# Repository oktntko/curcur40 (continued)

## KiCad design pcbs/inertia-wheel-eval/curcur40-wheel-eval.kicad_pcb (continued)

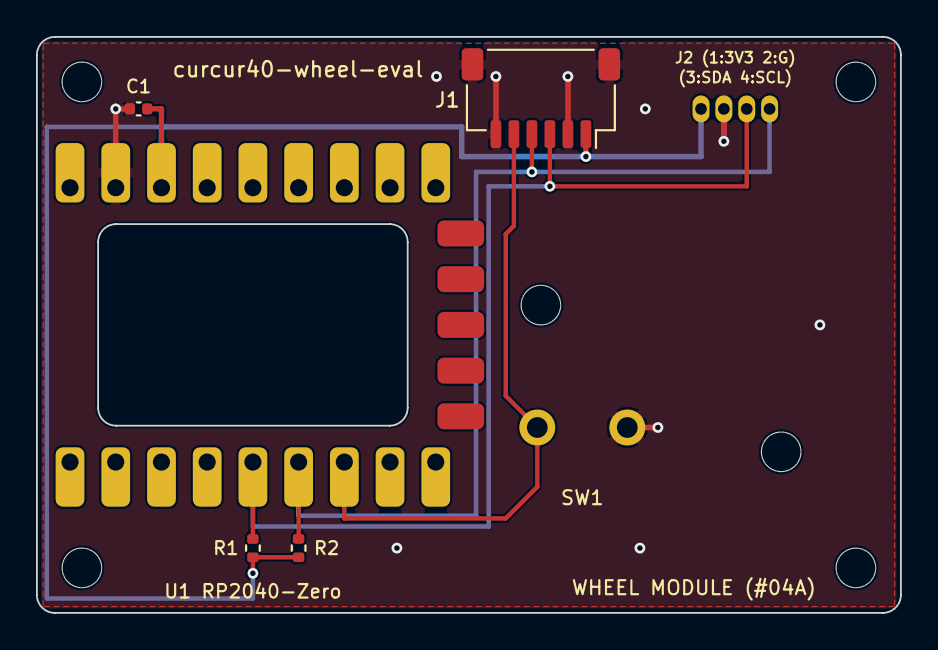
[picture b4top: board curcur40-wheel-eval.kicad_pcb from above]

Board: 2 copper layers, 48.0 x 32.0 mm, 13 parts (0 on the bottom side), 5 nets.

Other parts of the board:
H1, H2, H3, H4, H5, H6: MountingHole; MountingHole_2.2mm_M2

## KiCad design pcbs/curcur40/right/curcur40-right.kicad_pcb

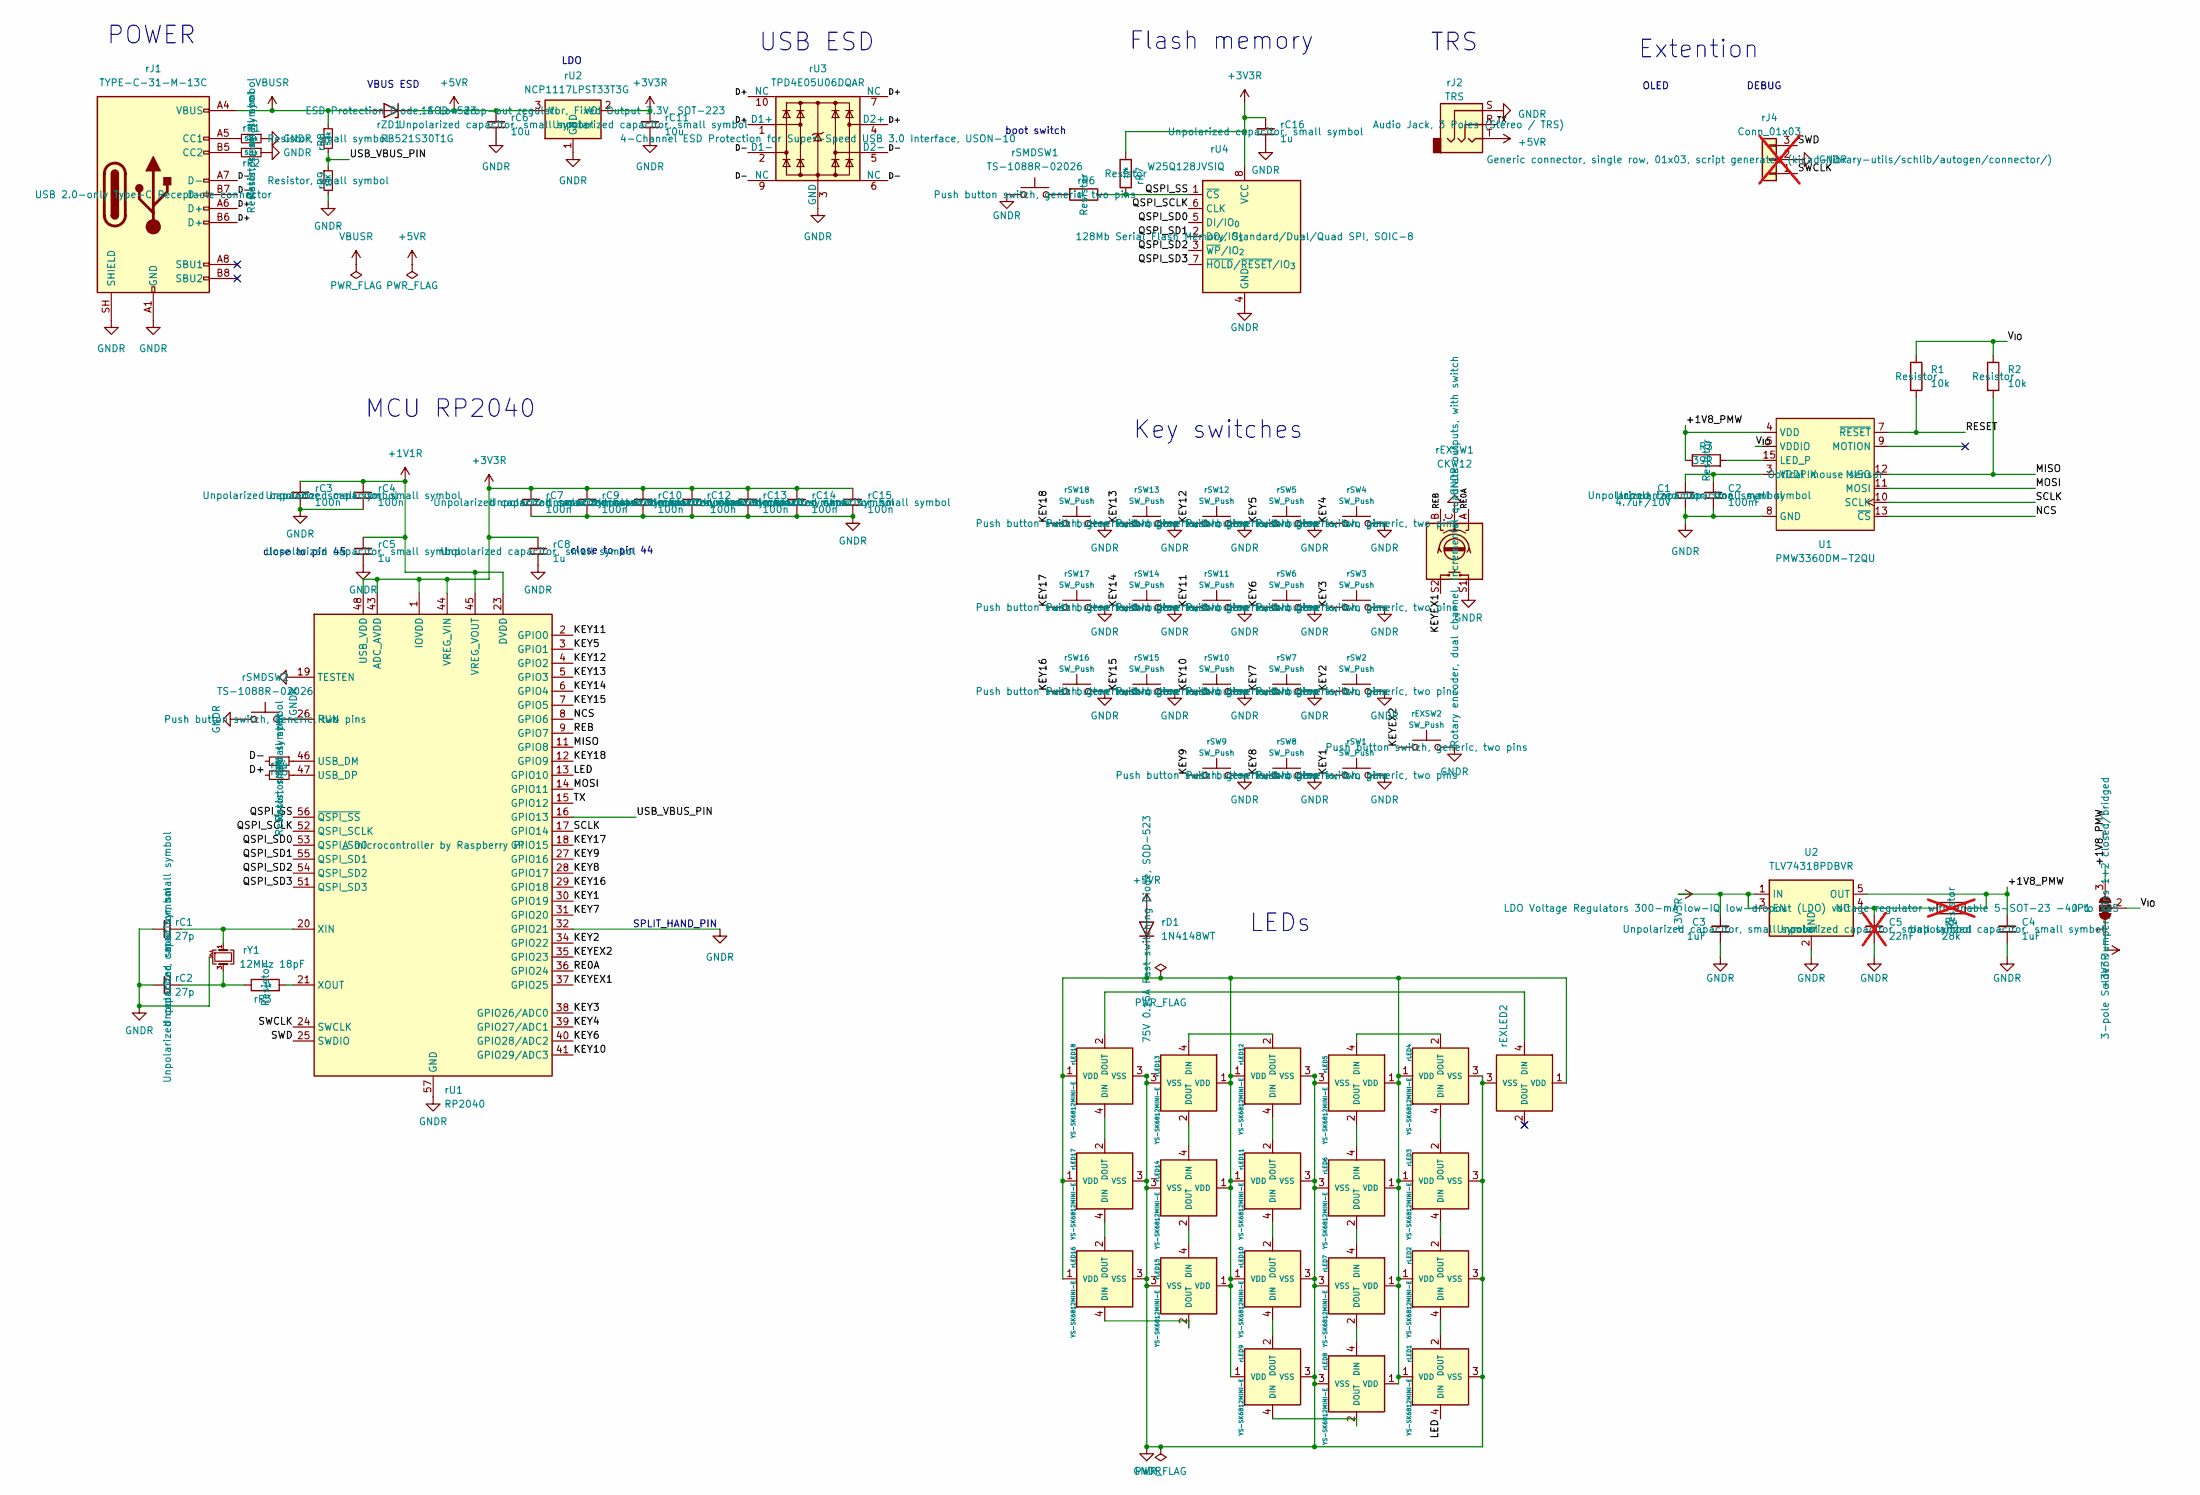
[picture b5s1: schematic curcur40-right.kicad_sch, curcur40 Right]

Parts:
C1: 4.7uF/10V; C_0603_1608Metric_Pad1.08x0.95mm_HandSolder; Mfr. # CL10A475KO8NNNC; LCSC C19666
C2: 100nF; C_0603_1608Metric_Pad1.08x0.95mm_HandSolder; Mfr. # CC0603KRX7R9BB104; LCSC C14663
C3, C4: 1uF; C_0603_1608Metric_Pad1.08x0.95mm_HandSolder; Mfr. # CL10A105KB8NNNC; LCSC C15849
C5: 22nF; C_0603_1608Metric_Pad1.08x0.95mm_HandSolder; Mfr. # CL10B223KB8NNNC; LCSC C21122; not fitted
JP1: SolderJumper_3_Bridged12; SolderJumper-3_P1.3mm_Bridged12_RoundedPad1.0x1.5mm_NumberL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
R1, R2: 10k; R_0603_1608Metric_Pad0.98x0.95mm_HandSolder; Mfr. # 0603WAF1002T5E; LCSC C25804
R3: 39R; R_0603_1608Metric_Pad0.98x0.95mm_HandSolder; Mfr. # 0603WAF390JT5E; LCSC C23154
R4: 28k; R_0603_1608Metric_Pad0.98x0.95mm_HandSolder; not fitted
U1: PMW3360DM-T2QU; PMW3360DM-T2QU_16Pin
U2: TLV74318PDBVR; SOT-23-5; Mfr. # TLV74318PDBVR; LCSC C485152
rC1, rC2: 27p; C_0402_1005Metric
rC3, rC4, rC7, rC9, rC10, rC12, rC13, rC14, rC15: 100n; C_0402_1005Metric
rC5, rC8, rC16: 1u; C_0402_1005Metric
rC6, rC11: 10u; C_0402_1005Metric
rD1: 1N4148WT; D_SOD-523; JLCPCB Part # C232841
rEXLED2: YS-SK6812MINI-E
rEXSW1: CKW12; RotaryEncoder_Switch_CKW12
rEXSW2: SW_Push; keyswitch_choc12_hotswap_1u
rJ1: TYPE-C-31-M-13C; USB_C_Receptacle_TYPE-C-31-M-13C; JLCPCB Part # C2848620
rJ2: TRS; Jack_PJ-398A-5A_PJ-399B-6A; JLCPCB Part # C128994
rJ4: Conn_01x03; PinHeader_1x03_P2.54mm_Vertical; not fitted
rLED1, rLED2, rLED3, rLED4, rLED5, rLED6, rLED7, rLED8, rLED9, rLED10, rLED11, rLED12, rLED13, rLED14, rLED15, rLED16, rLED17, rLED18: YS-SK6812MINI-E
rR1, rR2: 5.1k; R_0402_1005Metric
rR3, rR6: 1k; R_0402_1005Metric
rR4, rR5: 27; R_0402_1005Metric
rR7: 10k; R_0402_1005Metric
rR8: 5.6k; R_0402_1005Metric
rR9: 10K; R_0402_1005Metric
rSMDSW1, rSMDSW2: TS-1088R-02026; JLCPCB Part # C455280
rSW1, rSW2, rSW3, rSW4, rSW5, rSW6, rSW7, rSW8, rSW9, rSW10, rSW11, rSW12, rSW13, rSW14, rSW15, rSW16, rSW17, rSW18: SW_Push; keyswitch_choc12_hotswap_1u
rU1: RP2040; QFN-56-1EP_7x7mm_P0.4mm_EP3.2x3.2mm; JLCPCB Part # C2040
rU2: NCP1117LPST33T3G; SOT-223-3_TabPin2; JLCPCB Part # C146799
rU3: TPD4E05U06DQAR; USON-10_2.5x1.0mm_P0.5mm; JLCPCB Part # C138714
rU4: W25Q128JVSIQ; SOIC-8_5.3x5.3mm_P1.27mm; JLCPCB Part # C113767
rY1: 12MHz 18pF; Crystal_SMD_3225-4Pin_3.2x2.5mm; MFR.Part # Q22FA23V0041800; JLCPCB Part # C91749
rZD1: RB521S30T1G; D_SOD-523; JLCPCB Part # C145179

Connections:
+1V1R: rC3.1, rC4.1, rC5.1, rU1.23 (DVDD), rU1.45 (VREG_VOUT), rU1.50 (DVDD)
+3V3R: C3.1, JP1.1 (A), U2.1 (IN), U2.3 (EN), rC7.1, rC8.1, rC9.1, rC10.1, rC11.1, rC12.1, rC13.1, rC14.1, rC15.1, rC16.1, rR7.2, rU1.1 (IOVDD), rU1.10 (IOVDD), rU1.22 (IOVDD), rU1.33 (IOVDD), rU1.42 (IOVDD), rU1.43 (ADC_AVDD), rU1.44 (VREG_VIN), rU1.48 (USB_VDD), rU1.49 (IOVDD), rU2.2 (VO), rU4.8 (VCC)
+5VR: rC6.1, rD1.2 (A), rJ2.T, rU2.3 (VI), rZD1.1 (K)
/+1V8_PMW: C4.1, JP1.3 (B), R3.1, R4.1, U1.4 (VDD), U2.5 (OUT)
/D+: rJ1.A6 (D+), rJ1.B6 (D+), rR4.1, rU3.1 (D1+), rU3.4 (D2+), rU3.7 (NC), rU3.10 (NC)
/D-: rJ1.A7 (D-), rJ1.B7 (D-), rR5.2, rU3.2 (D1-), rU3.5 (D2-), rU3.6 (NC), rU3.9 (NC)
/KEY1: rSW1.1, rU1.30 (GPIO19)
/KEY2: rSW2.1, rU1.34 (GPIO22)
/KEY3: rSW3.1, rU1.38 (GPIO26/ADC0)
/KEY4: rSW4.1, rU1.39 (GPIO27/ADC1)
/KEY5: rSW5.1, rU1.3 (GPIO1)
/KEY6: rSW6.1, rU1.40 (GPIO28/ADC2)
/KEY7: rSW7.1, rU1.31 (GPIO20)
/KEY8: rSW8.1, rU1.28 (GPIO17)
/KEY9: rSW9.1, rU1.27 (GPIO16)
/KEY10: rSW10.1, rU1.41 (GPIO29/ADC3)
/KEY11: rSW11.1, rU1.2 (GPIO0)
/KEY12: rSW12.1, rU1.4 (GPIO2)
/KEY13: rSW13.1, rU1.5 (GPIO3)
/KEY14: rSW14.1, rU1.6 (GPIO4)
/KEY15: rSW15.1, rU1.7 (GPIO5)
/KEY16: rSW16.1, rU1.29 (GPIO18)
/KEY17: rSW17.1, rU1.18 (GPIO15)
/KEY18: rSW18.1, rU1.12 (GPIO9)
/KEYEX1: rEXSW1.S2, rU1.37 (GPIO25)
/KEYEX2: rEXSW2.1, rU1.35 (GPIO23)
/LED: rLED1.4 (DIN), rU1.13 (GPIO10)
/MISO: R2.2, U1.12 (MISO), rU1.11 (GPIO8)
/MOSI: U1.11 (MOSI), rU1.14 (GPIO11)
/NCS: U1.13 (~CS), rU1.8 (GPIO6)
/QSPI_SCLK: rU1.52 (QSPI_SCLK), rU4.6 (CLK)
/QSPI_SD0: rU1.53 (QSPI_SD0), rU4.5 (DI/IO_{0})
/QSPI_SD1: rU1.55 (QSPI_SD1), rU4.2 (DO/IO_{1})
/QSPI_SD2: rU1.54 (QSPI_SD2), rU4.3 (~WP/IO_{2})
/QSPI_SD3: rU1.51 (QSPI_SD3), rU4.7 (~HOLD/~RESET/IO_{3})
/QSPI_SS: rR6.1, rR7.1, rU1.56 (~QSPI_SS), rU4.1 (~CS)
/RE0A: rEXSW1.A, rU1.36 (GPIO24)
/REB: rEXSW1.B, rU1.9 (GPIO7)
/RESET: R1.2, U1.7 (~RESET)
/SCLK: U1.10 (SCLK), rU1.17 (GPIO14)
/SWCLK: rJ4.1, rU1.24 (SWCLK)
/SWD: rJ4.3, rU1.25 (SWDIO)
/TX: rJ2.R, rU1.15 (GPIO12)
/USB_VBUS_PIN: rR8.2, rR9.1, rU1.16 (GPIO13)
/V_{IO}: JP1.2 (C), R1.1, R2.1, U1.5 (VDDIO)
GNDR: C1.2, C2.2, C3.2, C4.2, C5.2, U1.8 (GND), U2.2 (GND), rC1.2, rC2.2, rC3.2, rC4.2, rC5.2, rC6.2, rC7.2, rC8.2, rC9.2, rC10.2, rC11.2, rC12.2, rC13.2, rC14.2, rC15.2, rC16.2, rEXLED2.3 (VSS), rEXSW1.C, rEXSW1.S1, rEXSW2.2, rJ1.A1 (GND), rJ1.A12 (GND), rJ1.B1 (GND), rJ1.B12 (GND), rJ1.SH (SHIELD), rJ2.S, rJ4.2, rLED1.3 (VSS), rLED2.3 (VSS), rLED3.3 (VSS), rLED4.3 (VSS), rLED5.3 (VSS), rLED6.3 (VSS), rLED7.3 (VSS), rLED8.3 (VSS), rLED9.3 (VSS), rLED10.3 (VSS), rLED11.3 (VSS), rLED12.3 (VSS), rLED13.3 (VSS), rLED14.3 (VSS), rLED15.3 (VSS), rLED16.3 (VSS), rLED17.3 (VSS), rLED18.3 (VSS), rR1.1, rR2.1, rR9.2, rSMDSW1.1, rSMDSW2.1, rSW1.2, rSW2.2, rSW3.2, rSW4.2, rSW5.2, rSW6.2, rSW7.2, rSW8.2, rSW9.2, rSW10.2, rSW11.2, rSW12.2, rSW13.2, rSW14.2, rSW15.2, rSW16.2, rSW17.2, rSW18.2, rU1.19 (TESTEN), rU1.32 (GPIO21), rU1.57 (GND), rU2.1 (GND), rU3.3 (GND), rU3.8 (GND), rU4.4 (GND), rY1.2 (G), rY1.4 (G)
unnamed: R3.2, U1.15 (LED_P)
unnamed: C1.1, C2.1, U1.3 (VDDPIX)
unnamed: C5.1, R4.2, U2.4 (NC)
unnamed: rC2.1, rR3.1, rY1.3
unnamed: rD1.1 (K), rEXLED2.1 (VDD), rLED1.1 (VDD), rLED2.1 (VDD), rLED3.1 (VDD), rLED4.1 (VDD), rLED5.1 (VDD), rLED6.1 (VDD), rLED7.1 (VDD), rLED8.1 (VDD), rLED9.1 (VDD), rLED10.1 (VDD), rLED11.1 (VDD), rLED12.1 (VDD), rLED13.1 (VDD), rLED14.1 (VDD), rLED15.1 (VDD), rLED16.1 (VDD), rLED17.1 (VDD), rLED18.1 (VDD)
unnamed: rEXLED2.4 (DIN), rLED18.2 (DOUT)
unnamed: rJ1.A5 (CC1), rR1.2
unnamed: rJ1.B5 (CC2), rR2.2
unnamed: rLED1.2 (DOUT), rLED2.4 (DIN)
unnamed: rLED2.2 (DOUT), rLED3.4 (DIN)
unnamed: rLED3.2 (DOUT), rLED4.4 (DIN)
unnamed: rLED4.2 (DOUT), rLED5.4 (DIN)
unnamed: rLED5.2 (DOUT), rLED6.4 (DIN)
unnamed: rLED6.2 (DOUT), rLED7.4 (DIN)
unnamed: rLED7.2 (DOUT), rLED8.4 (DIN)
unnamed: rLED8.2 (DOUT), rLED9.4 (DIN)
unnamed: rLED9.2 (DOUT), rLED10.4 (DIN)
unnamed: rLED10.2 (DOUT), rLED11.4 (DIN)
unnamed: rLED11.2 (DOUT), rLED12.4 (DIN)
unnamed: rLED12.2 (DOUT), rLED13.4 (DIN)
unnamed: rLED13.2 (DOUT), rLED14.4 (DIN)
unnamed: rLED14.2 (DOUT), rLED15.4 (DIN)
unnamed: rLED15.2 (DOUT), rLED16.4 (DIN)
unnamed: rLED16.2 (DOUT), rLED17.4 (DIN)
unnamed: rLED17.2 (DOUT), rLED18.4 (DIN)
unnamed: rR6.2, rSMDSW1.2
unnamed: rSMDSW2.2, rU1.26 (RUN)
unnamed: rR5.1, rU1.46 (USB_DM)
unnamed: rR4.2, rU1.47 (USB_DP)
unnamed: rC1.1, rU1.20 (XIN), rY1.1
unnamed: rR3.2, rU1.21 (XOUT)
VBUSR: rJ1.A4 (VBUS), rJ1.A9 (VBUS), rJ1.B4 (VBUS), rJ1.B9 (VBUS), rR8.1, rZD1.2 (A)

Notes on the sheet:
USB ESD
TRS
Flash memory
MCU RP2040
DEBUG
POWER
boot switch
LDO
Key switches
LEDs
Extention
VBUS ESD
OLED
close to pin 45
close to pin 44
SPLIT_HAND_PIN

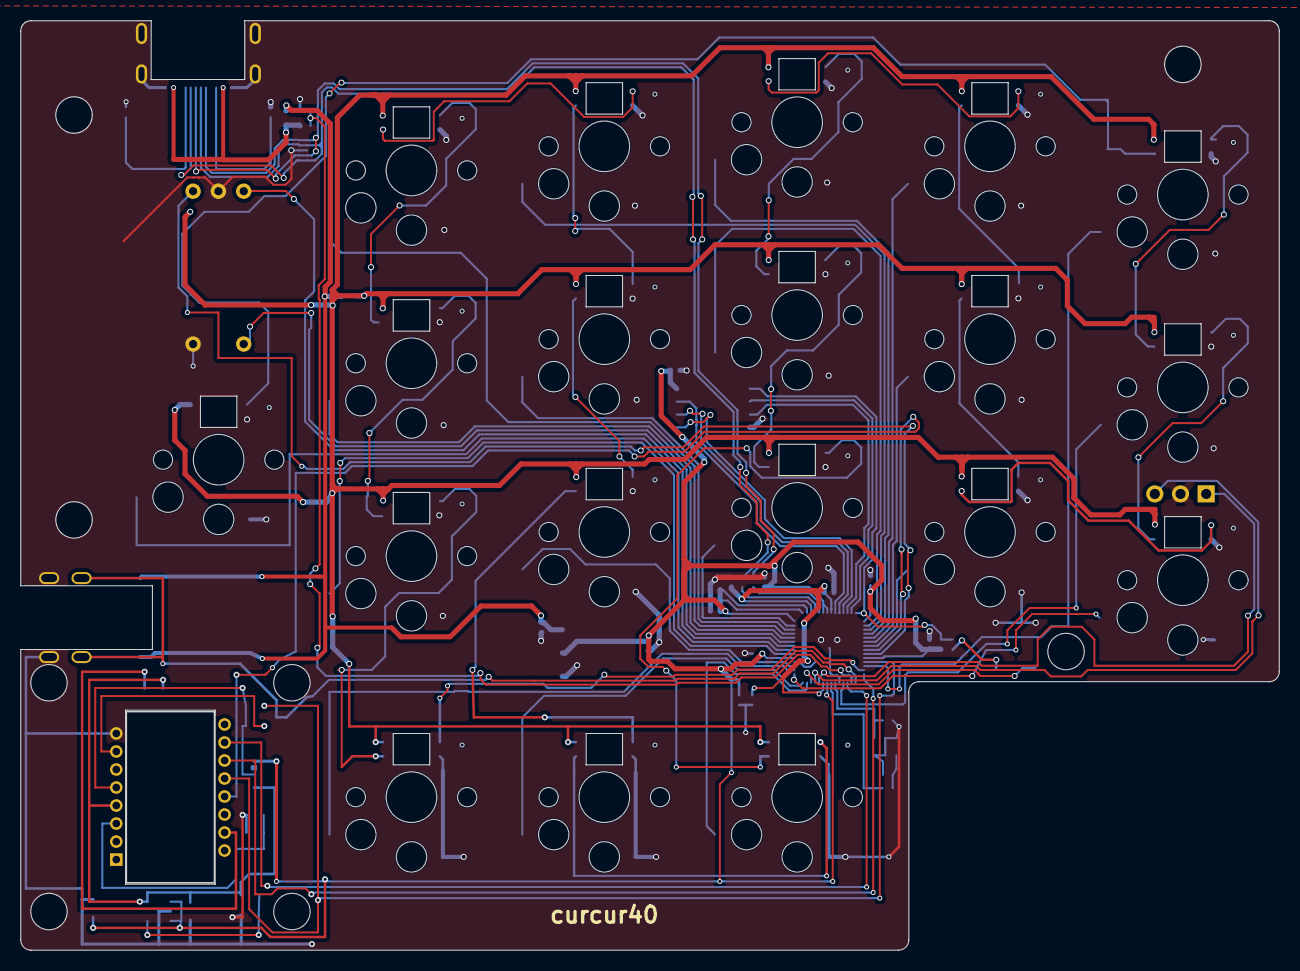
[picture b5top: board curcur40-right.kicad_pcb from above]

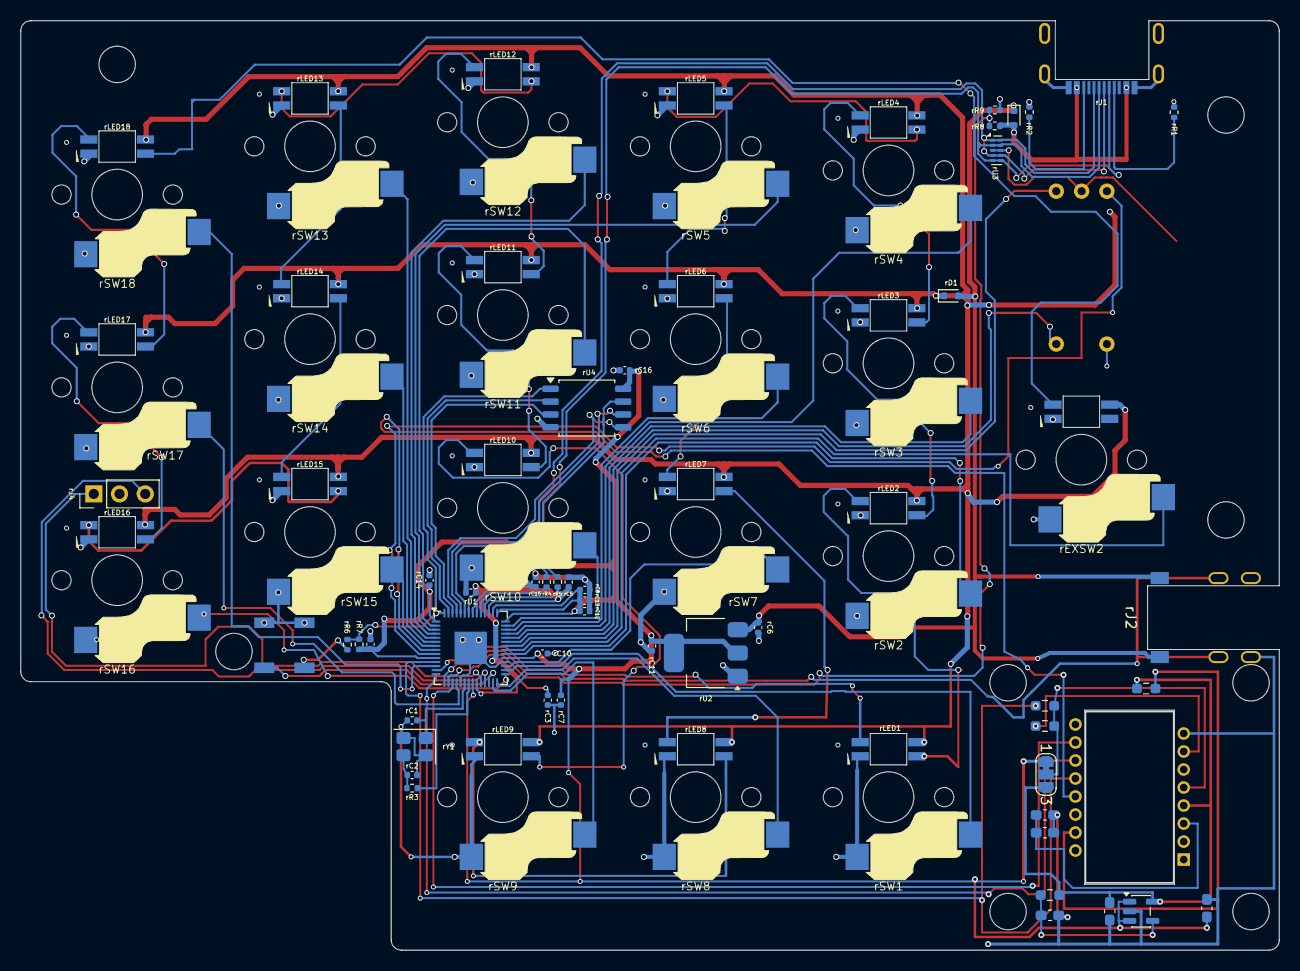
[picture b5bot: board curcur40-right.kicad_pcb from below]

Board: 2 copper layers, 124.3 x 91.8 mm, 88 parts (87 on the bottom side), 78 nets.

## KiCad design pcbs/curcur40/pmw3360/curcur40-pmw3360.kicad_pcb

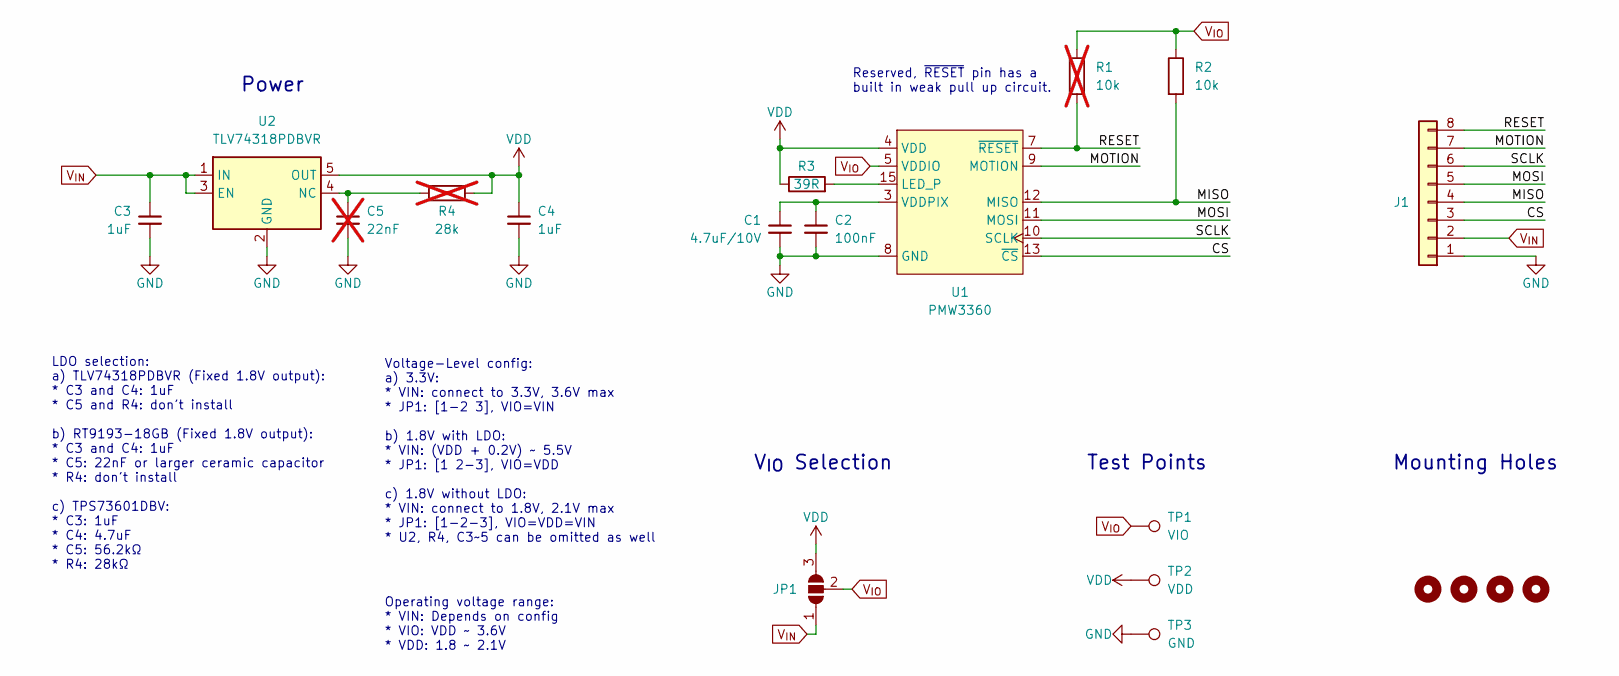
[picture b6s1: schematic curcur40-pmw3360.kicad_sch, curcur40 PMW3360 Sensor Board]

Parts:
C1: 4.7uF/10V; C_0603_1608Metric_Pad1.08x0.95mm_HandSolder; Mfr. # CL10A475KO8NNNC; LCSC C19666
C2: 100nF; C_0603_1608Metric_Pad1.08x0.95mm_HandSolder; Mfr. # CC0603KRX7R9BB104; LCSC C14663
C3, C4: 1uF; C_0603_1608Metric_Pad1.08x0.95mm_HandSolder; Mfr. # CL10A105KB8NNNC; LCSC C15849
C5: 22nF; C_0603_1608Metric_Pad1.08x0.95mm_HandSolder; Mfr. # CL10B223KB8NNNC; LCSC C21122; not fitted
H1, H2, H3, H4: MountingHole_2.2mm_M2
J1: Conn_01x08; PinHeader_1x08_P2.54mm_Vertical
JP1: SolderJumper_3_Open; SolderJumper-3_P1.3mm_Open_RoundedPad1.0x1.5mm_NumberLabels
R1: 10k; R_0603_1608Metric_Pad0.98x0.95mm_HandSolder; Mfr. # 0603WAF1002T5E; LCSC C25804; not fitted
R2: 10k; R_0603_1608Metric_Pad0.98x0.95mm_HandSolder; Mfr. # 0603WAF1002T5E; LCSC C25804
R3: 39R; R_0603_1608Metric_Pad0.98x0.95mm_HandSolder; Mfr. # 0603WAF390JT5E; LCSC C23154
R4: 28k; R_0603_1608Metric_Pad0.98x0.95mm_HandSolder; not fitted
TP1: VIO; TestPoint_Pad_D1.5mm
TP2: VDD; TestPoint_Pad_D1.5mm
TP3: GND; TestPoint_Pad_D1.5mm
U1: PMW3360; PMW3360DM-T2QU_16Pin; Mfr. # PMW3360DM-T2QU + LM19-LSI
U2: TLV74318PDBVR; SOT-23-5; Mfr. # TLV74318PDBVR; LCSC C485152

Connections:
/CS: J1.3, U1.13 (~CS)
/MISO: J1.4, R2.2, U1.12 (MISO)
/MOSI: J1.5, U1.11 (MOSI)
/MOTION: J1.7, U1.9 (MOTION)
/RESET: J1.8, R1.2, U1.7 (~RESET)
/SCLK: J1.6, U1.10 (SCLK)
GND: C1.2, C2.2, C3.2, C4.2, C5.2, J1.1, TP3.1, U1.8 (GND), U2.2 (GND)
unnamed: R3.2, U1.15 (LED_P)
unnamed: C1.1, C2.1, U1.3 (VDDPIX)
unnamed: C5.1, R4.2, U2.4 (NC)
VDD: C4.1, JP1.3 (B), R3.1, R4.1, TP2.1, U1.4 (VDD), U2.5 (OUT)
V_{IN}: C3.1, J1.2, JP1.1 (A), U2.1 (IN), U2.3 (EN)
V_{IO}: JP1.2 (C), R1.1, R2.1, TP1.1, U1.5 (VDDIO)

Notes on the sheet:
Voltage-Level config: a) 3.3V: * VIN: connect to 3.3V, 3.6V max * JP1: [1-2 3], VIO=VIN b) 1.8V with LDO: * VIN: (VDD + 0.2V) ~ 5.5V * JP1: [1 2-3], VIO=VDD c) 1.8V without LDO: * VIN: connect to 1.8V, 2.1V max * JP1: [1-2-3], VIO=VDD=VIN * U2, R4, C3~5 can be omitted as well
Operating voltage range: * VIN: Depends on config * VIO: VDD ~ 3.6V * VDD: 1.8 ~ 2.1V
V_{IO} Selection
LDO selection: a) TLV74318PDBVR (Fixed 1.8V output): * C3 and C4: 1uF * C5 and R4: don't install b) RT9193-18GB (Fixed 1.8V output): * C3 and C4: 1uF * C5: 22nF or larger ceramic capacitor * R4: don't install c) TPS73601DBV: * C3: 1uF * C4: 4.7uF * C5: 56.2kΩ * R4: 28kΩ
Reserved, ~{RESET} pin has a built in weak pull up circuit.
Test Points
Mounting Holes
Power

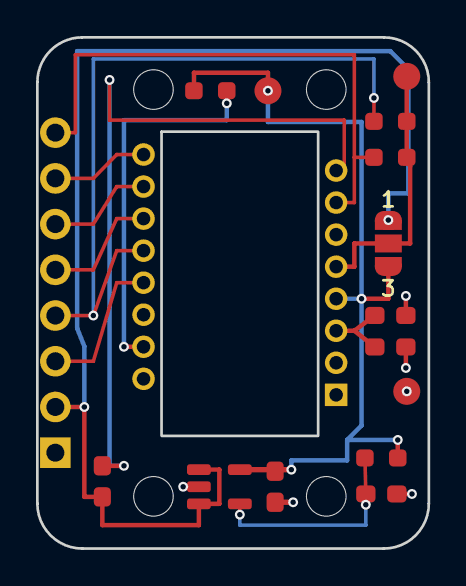
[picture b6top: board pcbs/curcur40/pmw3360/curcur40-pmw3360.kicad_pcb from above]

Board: 2 copper layers, 21.8 x 28.4 mm, 20 parts (0 on the bottom side), 13 nets.

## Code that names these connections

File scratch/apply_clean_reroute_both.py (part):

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        if net == "GNDR" and abs(sx - 111.5625) < 0.2 and abs(sy - 36.82625) < 0.2:
            to_delete.append(t)

        # Remove /KEY16 and /KEY17 tracks near pinky hole (98.0, 38.0)
        if net in ["/KEY16", "/KEY17"] and min(sx, ex) > 89.0 and max(sx, ex) < 102.0 and min(sy, ey) > 34.0 and max(sy, ey) < 41.0:
            to_delete.append(t)

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        if net == "+5V" and abs(sx - (-6.5425)) < 0.1 and abs(ex - (-6.5425)) < 0.1 and min(sy, ey) < 38.6 and max(sy, ey) > 30.7:
            to_delete.append(t)

        # Remove /KEY16, /KEY17, /KEY18 tracks near pinky hole (-98.0, 38.0)
        if net in ["/KEY16", "/KEY17", "/KEY18"] and min(sx, ex) > -103.0 and max(sx, ex) < -89.0 and min(sy, ey) > 34.0 and max(sy, ey) < 41.0:
            to_delete.append(t)

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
